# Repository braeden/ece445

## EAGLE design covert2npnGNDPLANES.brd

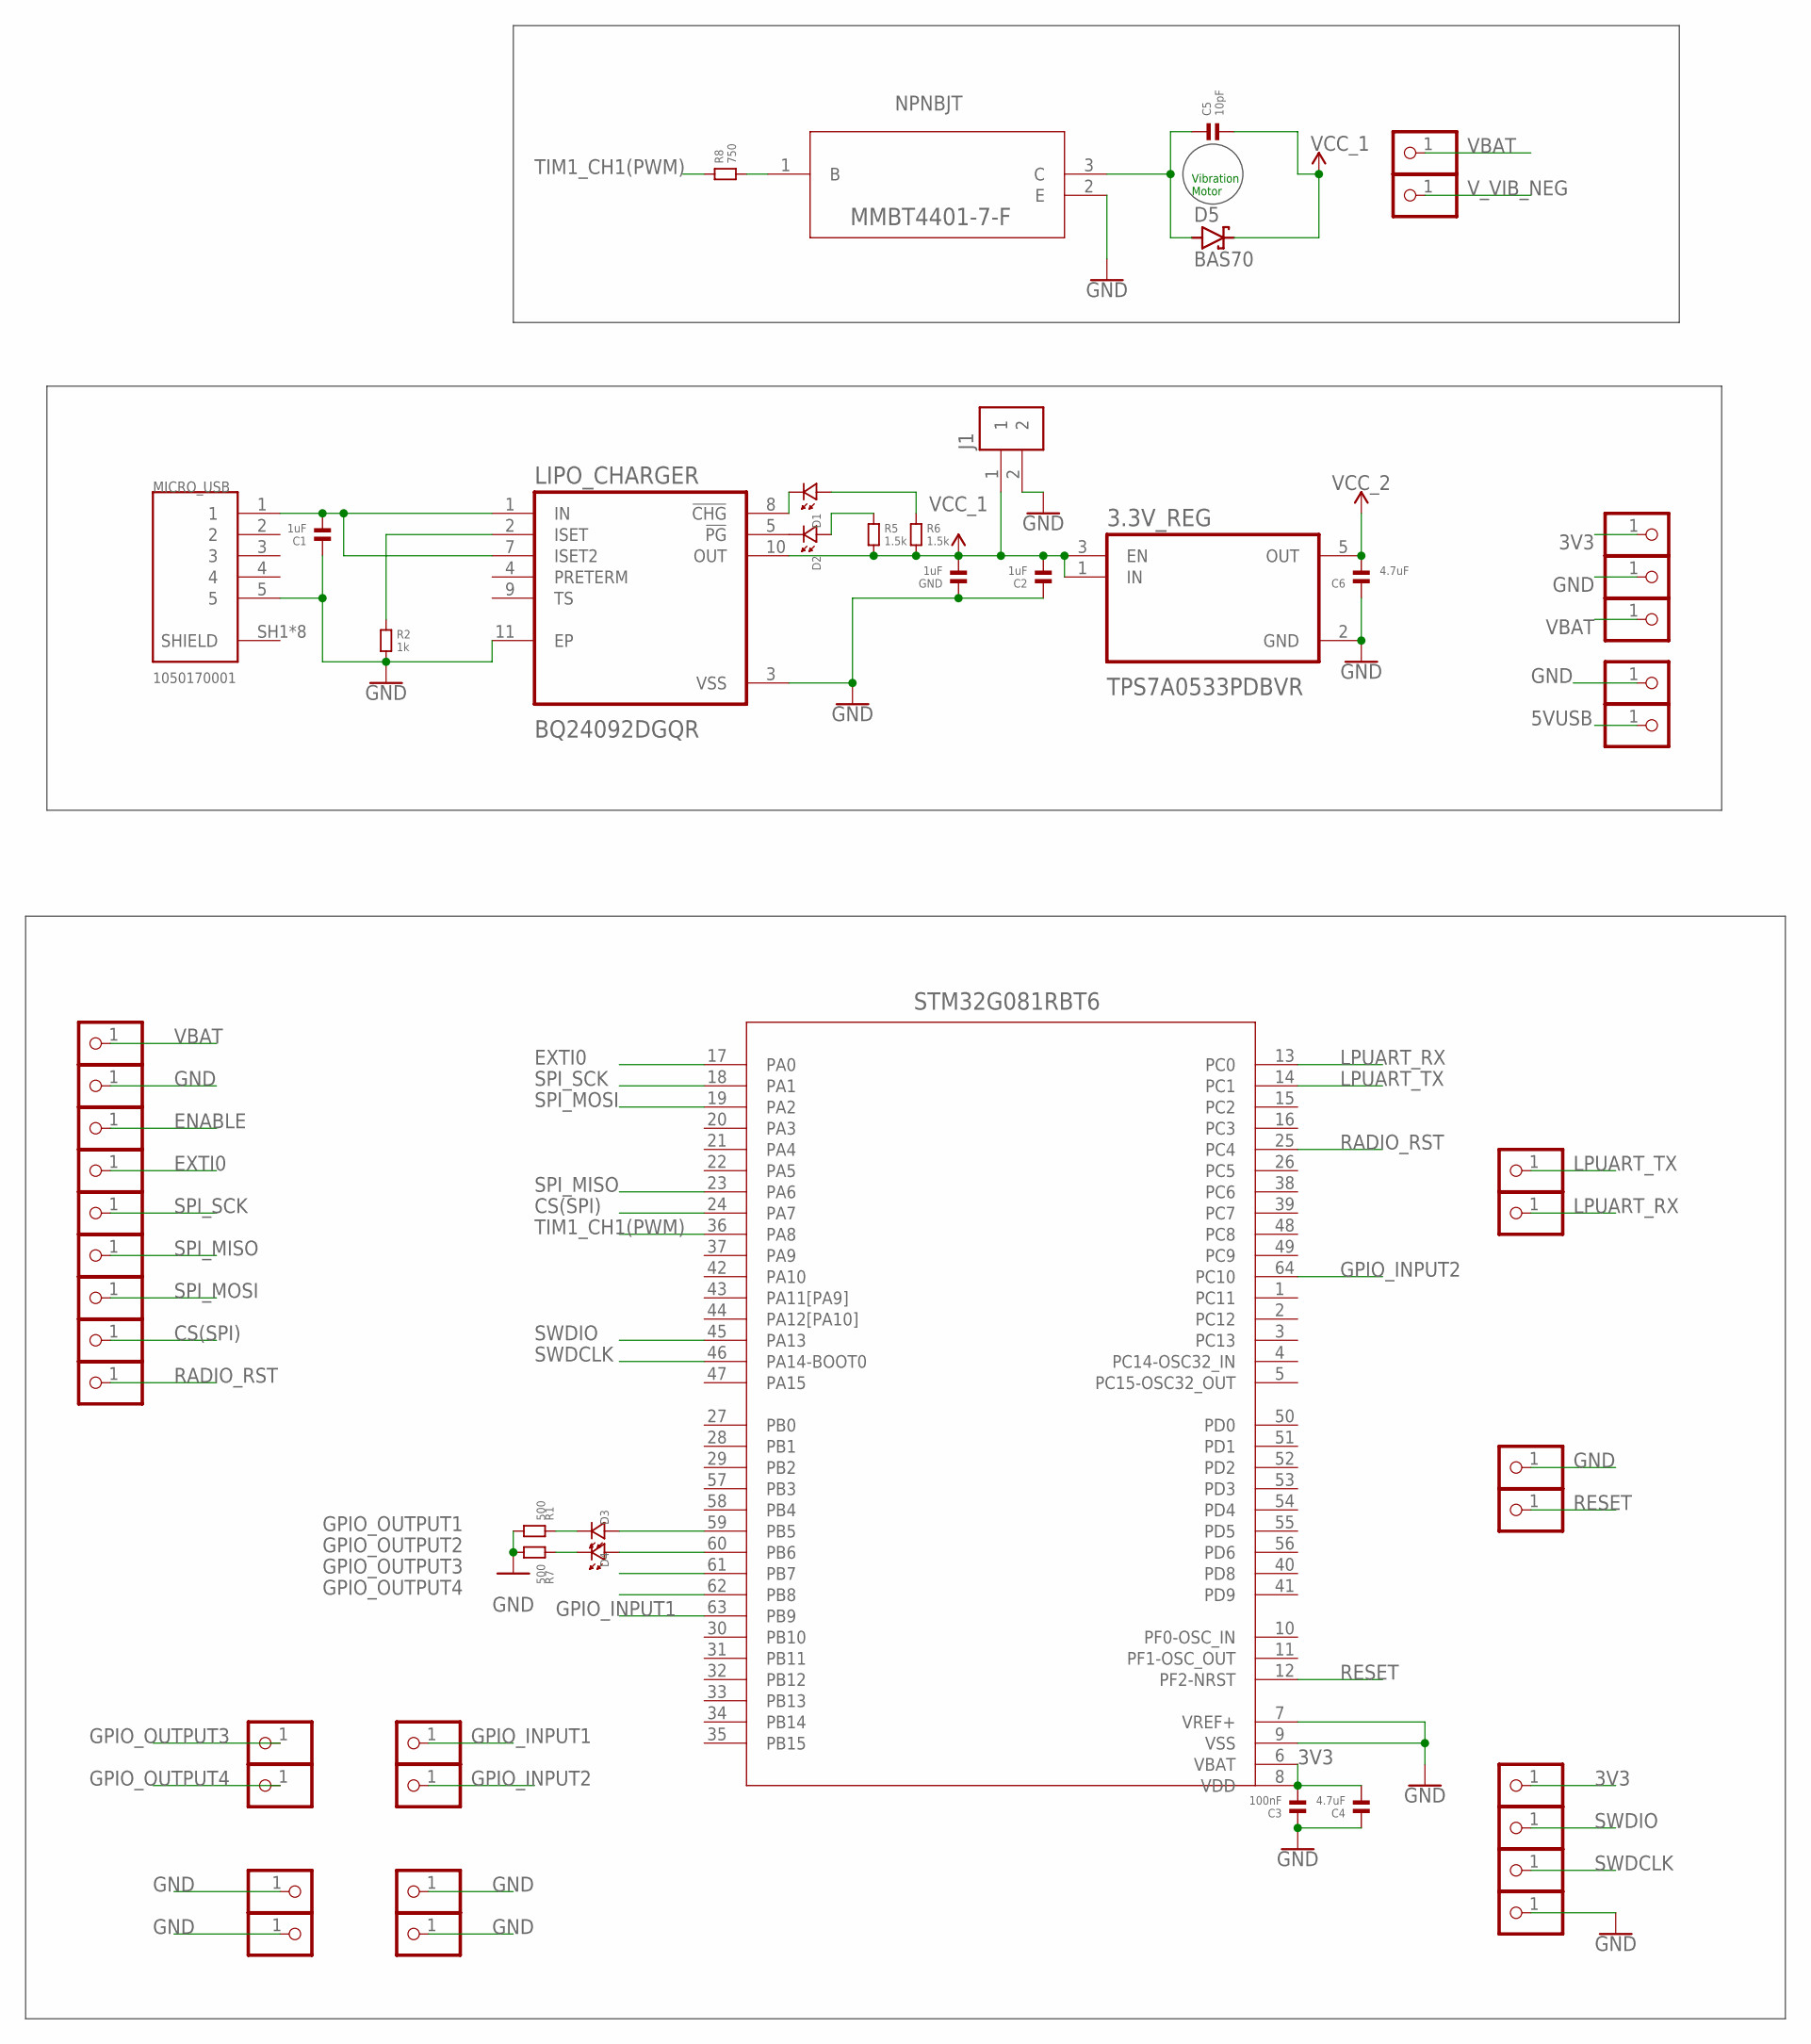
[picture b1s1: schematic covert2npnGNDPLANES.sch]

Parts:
3.3V_REG: TPS7A0533PDBVR; SOT95P280X145-5N
C1, C2: 1uF; 0805
C3: 100nF; 0805
C4, C6: 4.7uF; 0805
C5: 10pF; 0805
D1, D2, D3, D4: LED.0805; 0805.LED
D5: BAS70; SOT23
GND: 1uF; 0805
J1: B2B-PH-K-S(LF)(SN); JST_B2B-PH-K-S(LF)(SN)
JP1, JP2, JP3, JP4, JP5, JP6, JP7, JP8, JP9, JP10, JP11, JP12, JP13, JP14, JP15, JP16, JP17, JP18, JP19, JP20, JP21, JP22, JP23, JP24, JP26, JP27, JP28, JP29, JP30, JP31, JP32, JP33: PINHD-1X1; 1X01
LIPO_CHARGER: BQ24092DGQR; IC_XTR111AIDGQR
MICRO_USB: 1050170001; MOLEX_1050170001
R1, R7: 500; 0805
R2: 1k; 0805
R5, R6: 1.5k; 0805
R8: 750; 0805
U1: STM32G081RBT6; LQFP-64
U2: MMBT4401-7-F; SOT-23_DIO

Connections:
3V3: 3.3V_REG.5 (OUT), C3.2, C4.2, C6.2, JP4.1, JP16.1, U1.6 (VBAT), U1.8 (VDD)
5VUSB: C1.2, JP30.1, LIPO_CHARGER.1 (IN), LIPO_CHARGER.7 (ISET2), MICRO_USB.1
CS(SPI): JP6.1, U1.24 (PA7)
ENABLE: JP11.1
EXTI0: JP10.1, U1.17 (PA0)
GND: 3.3V_REG.2 (GND), C1.1, C2.1, C3.1, C4.1, C6.1, GND.1, J1.2, JP3.1, JP12.1, JP15.1, JP23.1, JP26.1, JP27.1, JP28.1, JP29.1, JP33.1, LIPO_CHARGER.3 (VSS), LIPO_CHARGER.11 (EP), MICRO_USB.5, R1.1, R2.2, R7.1, U1.7 (VREF+), U1.9 (VSS), U2.2 (E)
GPIO_INPUT1: JP17.1, U1.63 (PB9)
GPIO_INPUT2: JP18.1, U1.64 (PC10)
GPIO_OUTPUT1: D3.P$1 (1), U1.59 (PB5)
GPIO_OUTPUT2: D4.P$1 (1), U1.60 (PB6)
GPIO_OUTPUT3: JP19.1, U1.61 (PB7)
GPIO_OUTPUT4: JP20.1, U1.62 (PB8)
LPUART_RX: JP32.1, U1.13 (PC0)
LPUART_TX: JP31.1, U1.14 (PC1)
unnamed: LIPO_CHARGER.2 (ISET), R2.1
unnamed: D4.P$2 (2), R7.2
unnamed: D2.P$1 (1), R5.1
unnamed: D1.P$1 (1), R6.1
unnamed: D2.P$2 (2), LIPO_CHARGER.5 (!PG)
unnamed: R8.2, U2.1 (B)
unnamed: D3.P$2 (2), R1.2
unnamed: D1.P$2 (2), LIPO_CHARGER.8 (!CHG)
RADIO_RST: JP5.1, U1.25 (PC4)
RESET: JP24.1, U1.12 (PF2-NRST)
SPI_MISO: JP8.1, U1.23 (PA6)
SPI_MOSI: JP7.1, U1.19 (PA2)
SPI_SCK: JP9.1, U1.18 (PA1)
SWDCLK: JP2.1, U1.46 (PA14-BOOT0)
SWDIO: JP1.1, U1.45 (PA13)
TIM1_CH1(PWM): R8.1, U1.36 (PA8)
VBAT: 3.3V_REG.1 (IN), 3.3V_REG.3 (EN), C2.2, C5.2, D5.3 (C), GND.2, J1.1, JP13.1, JP14.1, JP21.1, LIPO_CHARGER.10 (OUT), R5.2, R6.2
V_VIB_NEG: C5.1, D5.1 (A), JP22.1, U2.3 (C)

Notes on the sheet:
Vibration Motor

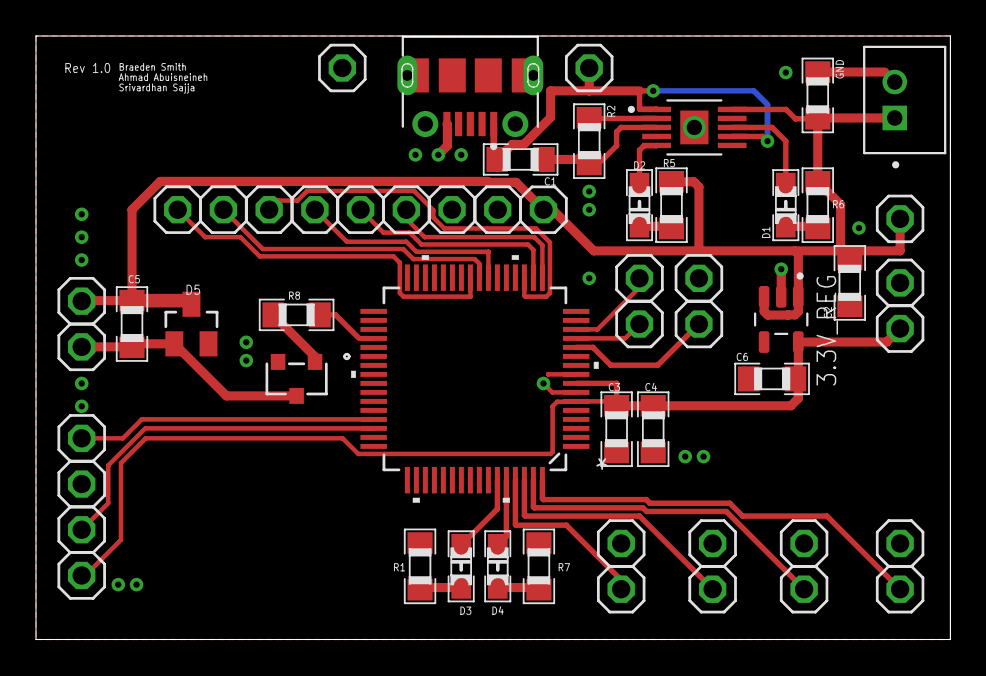
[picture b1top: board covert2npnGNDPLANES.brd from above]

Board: 2 copper layers, 50.8 x 33.5 mm, 56 parts (0 on the bottom side), 31 nets.

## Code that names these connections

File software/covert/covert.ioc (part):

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Mcu.Name=STM32G081RBTx
Mcu.Package=LQFP64
Mcu.UserName=STM32G081RBTx
PA0.GPIOParameters=GPIO_PuPd,GPIO_Label,GPIO_ModeDefaultEXTI
PA0.GPIO_Label=RADIO_INT
PA0.GPIO_ModeDefaultEXTI=GPIO_MODE_IT_RISING
PA0.GPIO_PuPd=GPIO_PULLDOWN
PA0.Signal=GPXTI0
PA1.Mode=Full_Duplex_Master
PA1.Signal=SPI1_SCK
PA13.Mode=Serial_Wire
PA13.Signal=SYS_SWDIO
PA14-BOOT0.Mode=Serial_Wire
PA14-BOOT0.Signal=SYS_SWCLK
PA2.Mode=Full_Duplex_Master
PA2.Signal=SPI1_MOSI
PA6.Mode=Full_Duplex_Master
PA6.Signal=SPI1_MISO
PA7.GPIOParameters=GPIO_PuPd,GPIO_Label
PA7.GPIO_Label=RADIO_CS
PA7.GPIO_PuPd=GPIO_PULLUP
PA7.Signal=GPIO_Output
PA8.GPIOParameters=GPIO_Label
PA8.GPIO_Label=VIBE_PWM
PA8.Signal=S_TIM1_CH1
PB13.GPIOParameters=GPIO_PuPd,GPIO_Label,GPIO_ModeDefaultEXTI
PB13.GPIO_Label=PAIR
PB13.GPIO_ModeDefaultEXTI=GPIO_MODE_IT_FALLING
PB13.GPIO_PuPd=GPIO_PULLUP
PB13.Signal=GPXTI13
PB8.GPIOParameters=GPIO_PuPd,GPIO_Label,GPIO_ModeDefaultEXTI
PB8.GPIO_Label=VIBE_BUTTON
PB8.GPIO_ModeDefaultEXTI=GPIO_MODE_IT_FALLING
PB8.GPIO_PuPd=GPIO_PULLUP
PB8.Signal=GPXTI8
PB9.GPIOParameters=GPIO_Label
PB9.GPIO_Label=LED1
PB9.Signal=GPIO_Output
PC10.GPIOParameters=GPIO_Label
PC10.GPIO_Label=LED2
PC10.Signal=GPIO_Output
PC4.GPIOParameters=GPIO_Label
PC4.GPIO_Label=RADIO_RESET
PC4.Signal=GPIO_Output
RCC.HSE_VALUE=8000000
RCC.SYSCLKFreq_VALUE=64000000
RCC.SYSCLKSource=RCC_SYSCLKSOURCE_PLLCLK
board=custom

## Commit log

2021-02-27 finished initial schematic + PCB
2021-03-02 mostly final state
2021-03-09 some more fixes
2021-03-13 Mounting, silkscreen, moved LEDS
2021-03-13 pairing button
2021-03-16 move leds
2021-03-16 move leds2
2021-03-16 Add files via upload
    CAD schematic for the device (without casing)
2021-03-17 Added .obj for casing (to 3D print)
2021-03-18 clean up
2021-03-18 clean up2
2021-03-18 move into folder
2021-03-18 remove
2021-03-18 readme
2021-04-06 gerbers+rev2
2021-04-15 added RFM95 custom library files
2021-04-19 added copy of software project
2021-04-20 working even better
2021-04-22 more fixes, packeting with preambles, fix sequence number & misalign
2021-04-28 final commit

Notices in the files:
parts and their libraries:
COPYRIGHT: Copyright (C) 2018 Accelerated Designs. All rights reserved
SparkFun-PowerSymbols: Licensing: Creative Commons ShareAlike 4.0 International - https://creativecommons.org/licenses/by-sa/4.0
